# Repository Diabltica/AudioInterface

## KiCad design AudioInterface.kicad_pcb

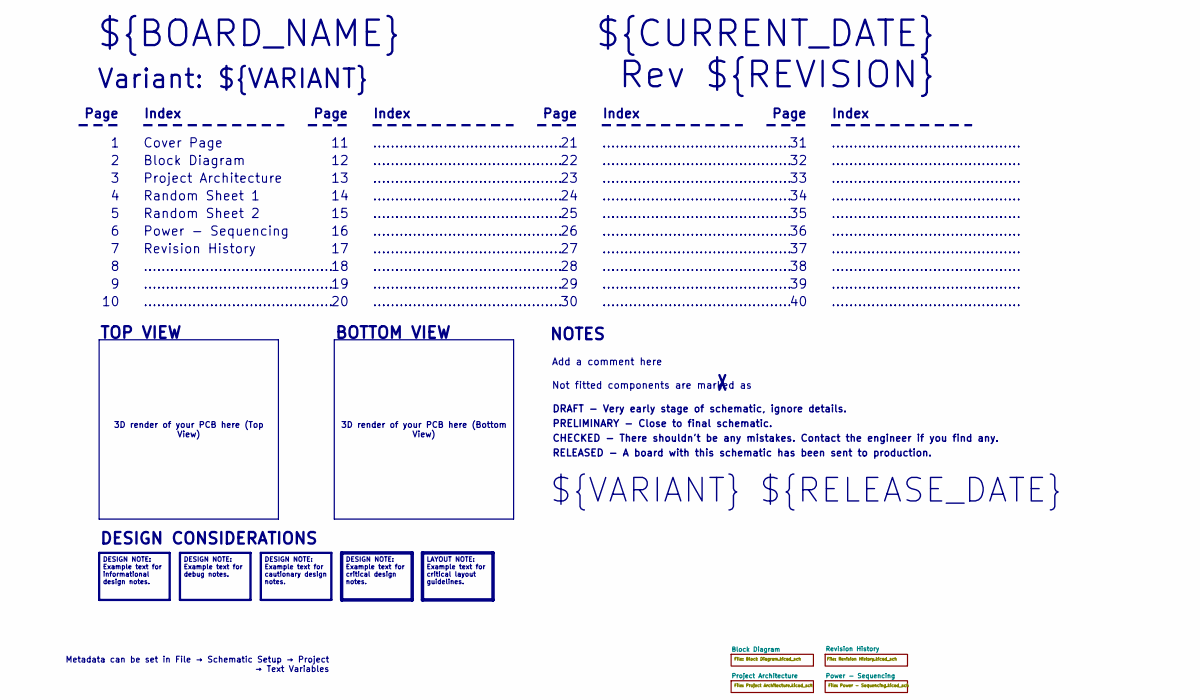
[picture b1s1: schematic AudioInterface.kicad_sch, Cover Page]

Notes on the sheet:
3D render of your PCB here (Bottom View)
3D render of your PCB here (Top View)
Metadata can be set in File → Schematic Setup → Project → Text Variables
DESIGN NOTE: Example text for informational design notes.
LAYOUT NOTE: Example text for critical layout guidelines.
DESIGN NOTE: Example text for cautionary design notes.
DESIGN NOTE: Example text for debug notes.
DESIGN NOTE: Example text for critical design notes.
BOTTOM VIEW
...........................................
RELEASED - A board with this schematic has been sent to production.
Page
TOP VIEW
Not fitted components are marked as
Index
PRELIMINARY - Close to final schematic.
${VARIANT} ${RELEASE_DATE}
Random Sheet 1
${CURRENT_DATE}
Variant: ${VARIANT}
Rev ${REVISION}
Random Sheet 2
${BOARD_NAME}
DRAFT - Very early stage of schematic, ignore details.
Power - Sequencing
Block Diagram
Add a comment here
Cover Page
NOTES
Project Architecture
CHECKED - There shouldn't be any mistakes. Contact the engineer if you find any.
DESIGN CONSIDERATIONS
Revision History

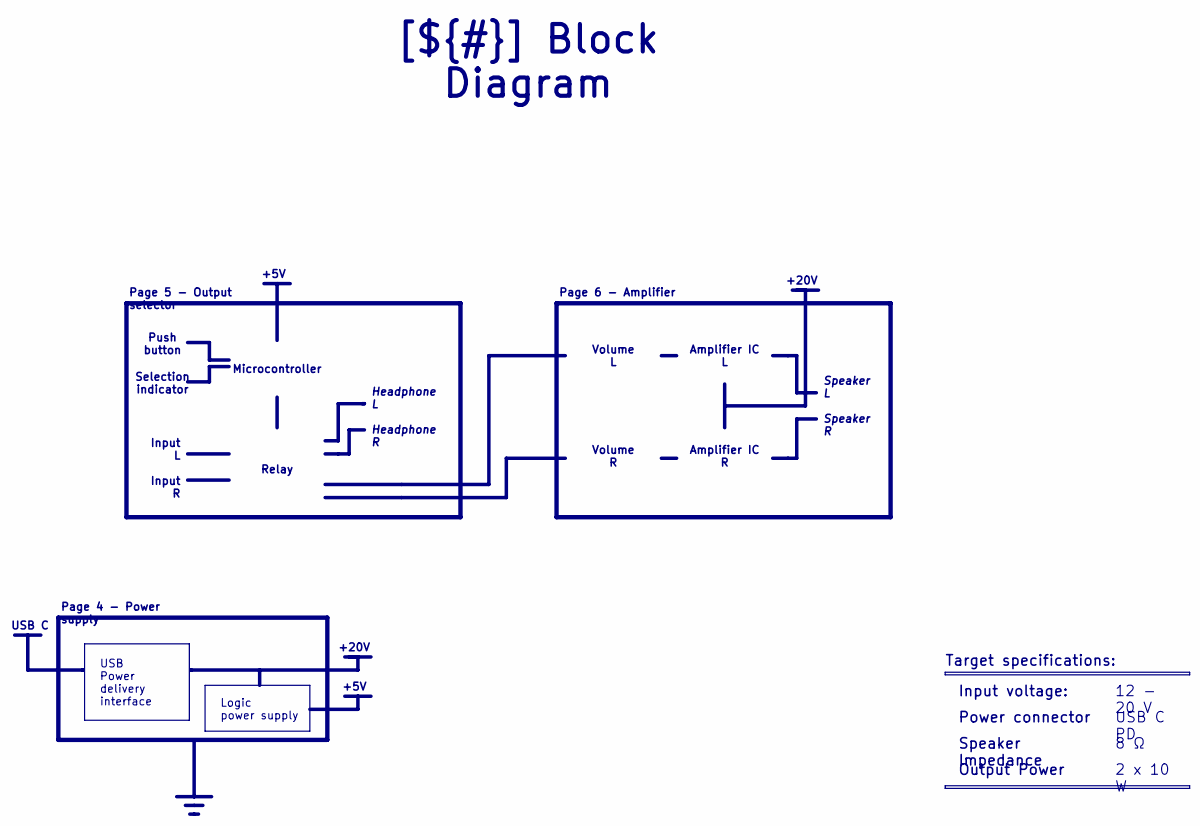
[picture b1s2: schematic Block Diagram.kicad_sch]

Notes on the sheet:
Page 5 - Output selector
Speaker Impedance
Power connector
Logic power supply
Input voltage:
2 x 10 W
USB C PD
Amplifier IC L
Volume L
Headphone L Headphone R
Microcontroller
[${#}] ${TITLE}
Page 4 - Power supply
Target specifications:
Selection indicator
8 Ω
Page 6 - Amplifier
12 - 20 V
Push button
Amplifier IC R
Relay
Input L Input R
Output Power
USB Power delivery interface
Volume R
Speaker L Speaker R
+20V
+5V
USB C

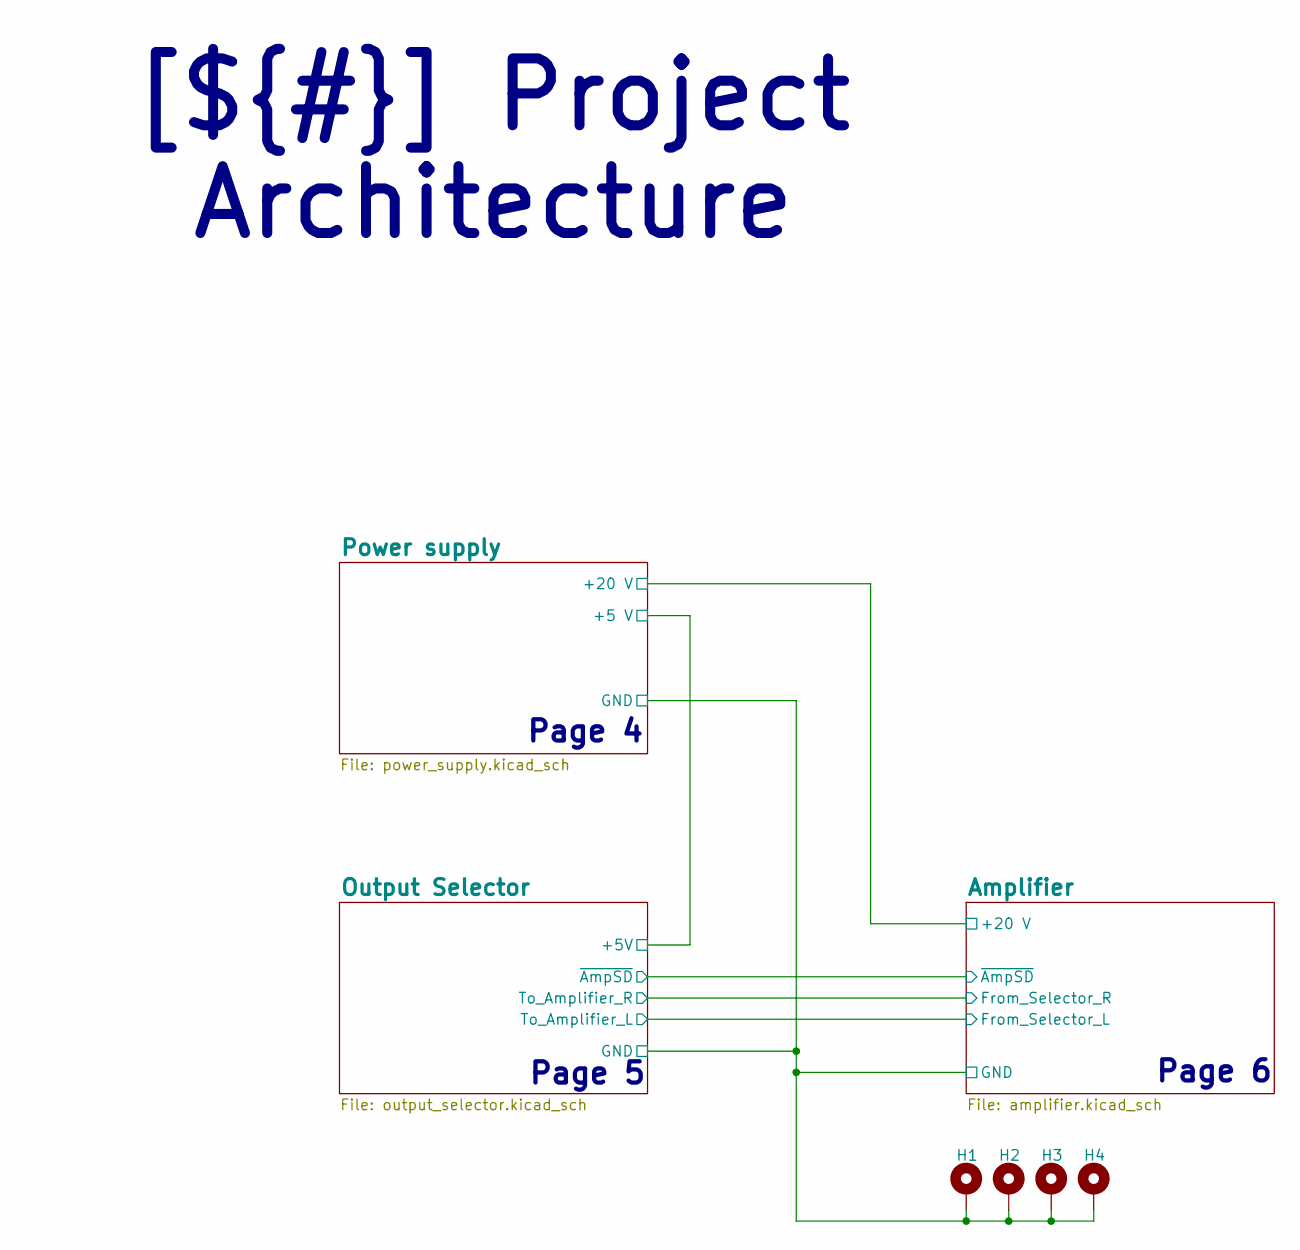
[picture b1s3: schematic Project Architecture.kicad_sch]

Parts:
H1, H2, H3, H4: MountingHole_Pad; MountingHole_3.2mm_M3_Pad_Via

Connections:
GND: H1.1, H2.1, H3.1, H4.1; also elsewhere on the board

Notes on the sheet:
[${#}] ${TITLE}
Page 6
Page 5
Page 4

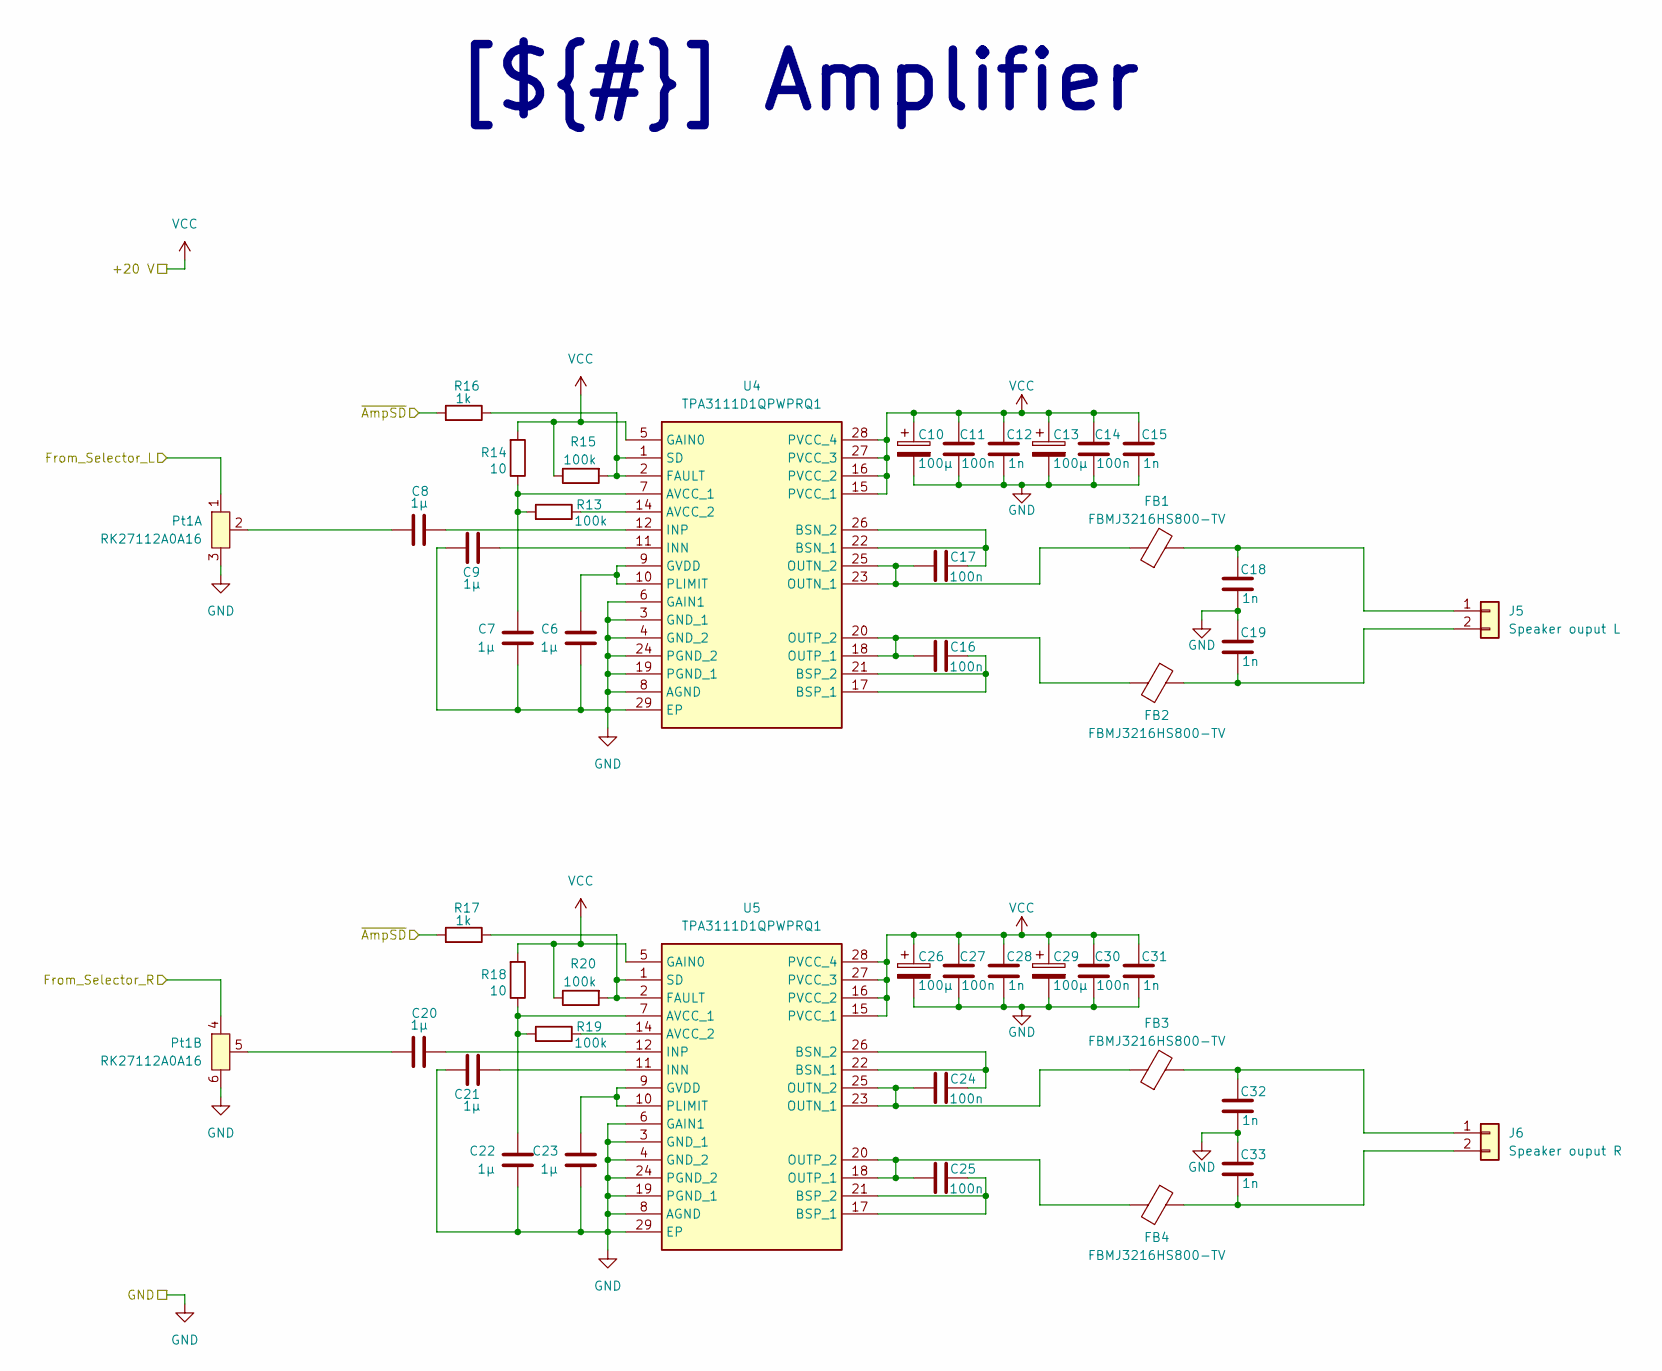
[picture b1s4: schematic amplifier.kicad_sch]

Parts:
C6, C7, C8, C9, C20, C21, C22, C23: 1µ; C_0402_1005Metric; LCSC Part C1518208
C10, C13, C26, C29: 100µ; CP_Elec_6.3x7.7; LCSC Part C178585
C11, C14, C16, C17, C24, C25, C27, C30: 100n; C_0402_1005Metric; LCSC Part C77020
C12, C15, C18, C19, C28, C31, C32, C33: 1n; C_0402_1005Metric; LCSC Part C77018
FB1, FB2, FB3, FB4: FBMJ3216HS800-TV; L_1206_3216Metric; LCSC C2661525
J5: Speaker ouput L; PinHeader_1x02_P2.54mm_Vertical
J6: Speaker ouput R; PinHeader_1x02_P2.54mm_Vertical
Pt1: RK27112A0A16; RES-ADJ-TH_RK27112A0A16; LCSC Part C470508
R13, R15, R19, R20: 100k; R_0402_1005Metric; LCSC Part C427253
R14, R18: 10; R_0402_1005Metric; LCSC Part C854481
R16, R17: 1k; R_0402_1005Metric; LCSC Part C427241
U4, U5: TPA3111D1QPWPRQ1; SOP65P640X120-29N; Mouser Part Number 595-TPA3111D1QPWPRQ1

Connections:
/Project Architecture/Amplifier/From_Selector_L: Pt1.1; also elsewhere on the board
/Project Architecture/Amplifier/From_Selector_R: Pt1.4; also elsewhere on the board
/Project Architecture/Amplifier/~AmpSD: R16.2, R17.2; also elsewhere on the board
GND: C6.1, C7.1, C9.2, C10.2, C11.1, C12.1, C13.2, C14.1, C15.1, C18.1, C19.2, C21.2, C22.1, C23.1, C26.2, C27.1, C28.1, C29.2, C30.1, C31.1, C32.1, C33.2, Pt1.3, Pt1.6, U4.3 (GND_1), U4.4 (GND_2), U4.6 (GAIN1), U4.8 (AGND), U4.19 (PGND_1), U4.24 (PGND_2), U4.29 (EP), U5.3 (GND_1), U5.4 (GND_2), U5.6 (GAIN1), U5.8 (AGND), U5.19 (PGND_1), U5.24 (PGND_2), U5.29 (EP); also elsewhere on the board
unnamed: C8.1, Pt1.2
unnamed: C20.1, Pt1.5
unnamed: C18.2, FB1.2, J5.1
unnamed: C19.1, FB2.1, J5.2
unnamed: C32.2, FB3.2, J6.1
unnamed: C33.1, FB4.1, J6.2
unnamed: C7.2, R13.2, R14.1, U4.7 (AVCC_1)
unnamed: R13.1, U4.14 (AVCC_2)
unnamed: C17.1, U4.22 (BSN_1), U4.26 (BSN_2)
unnamed: C16.1, U4.17 (BSP_1), U4.21 (BSP_2)
unnamed: R15.2, R16.1, U4.1 (SD), U4.2 (FAULT)
unnamed: C6.2, U4.9 (GVDD), U4.10 (PLIMIT)
unnamed: C9.1, U4.11 (INN)
unnamed: C8.2, U4.12 (INP)
unnamed: C17.2, FB1.1, U4.23 (OUTN_1), U4.25 (OUTN_2)
unnamed: C16.2, FB2.2, U4.18 (OUTP_1), U4.20 (OUTP_2)
unnamed: C22.2, R18.1, R19.2, U5.7 (AVCC_1)
unnamed: R19.1, U5.14 (AVCC_2)
unnamed: C24.1, U5.22 (BSN_1), U5.26 (BSN_2)
unnamed: C25.1, U5.17 (BSP_1), U5.21 (BSP_2)
unnamed: R17.1, R20.2, U5.1 (SD), U5.2 (FAULT)
unnamed: C23.2, U5.9 (GVDD), U5.10 (PLIMIT)
unnamed: C21.1, U5.11 (INN)
unnamed: C20.2, U5.12 (INP)
unnamed: C24.2, FB3.1, U5.23 (OUTN_1), U5.25 (OUTN_2)
unnamed: C25.2, FB4.2, U5.18 (OUTP_1), U5.20 (OUTP_2)
VCC: C10.1, C11.2, C12.2, C13.1, C14.2, C15.2, C26.1, C27.2, C28.2, C29.1, C30.2, C31.2, R14.2, R15.1, R18.2, R20.1, U4.5 (GAIN0), U4.15 (PVCC_1), U4.16 (PVCC_2), U4.27 (PVCC_3), U4.28 (PVCC_4), U5.5 (GAIN0), U5.15 (PVCC_1), U5.16 (PVCC_2), U5.27 (PVCC_3), U5.28 (PVCC_4); also elsewhere on the board

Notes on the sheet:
[${#}] ${TITLE}

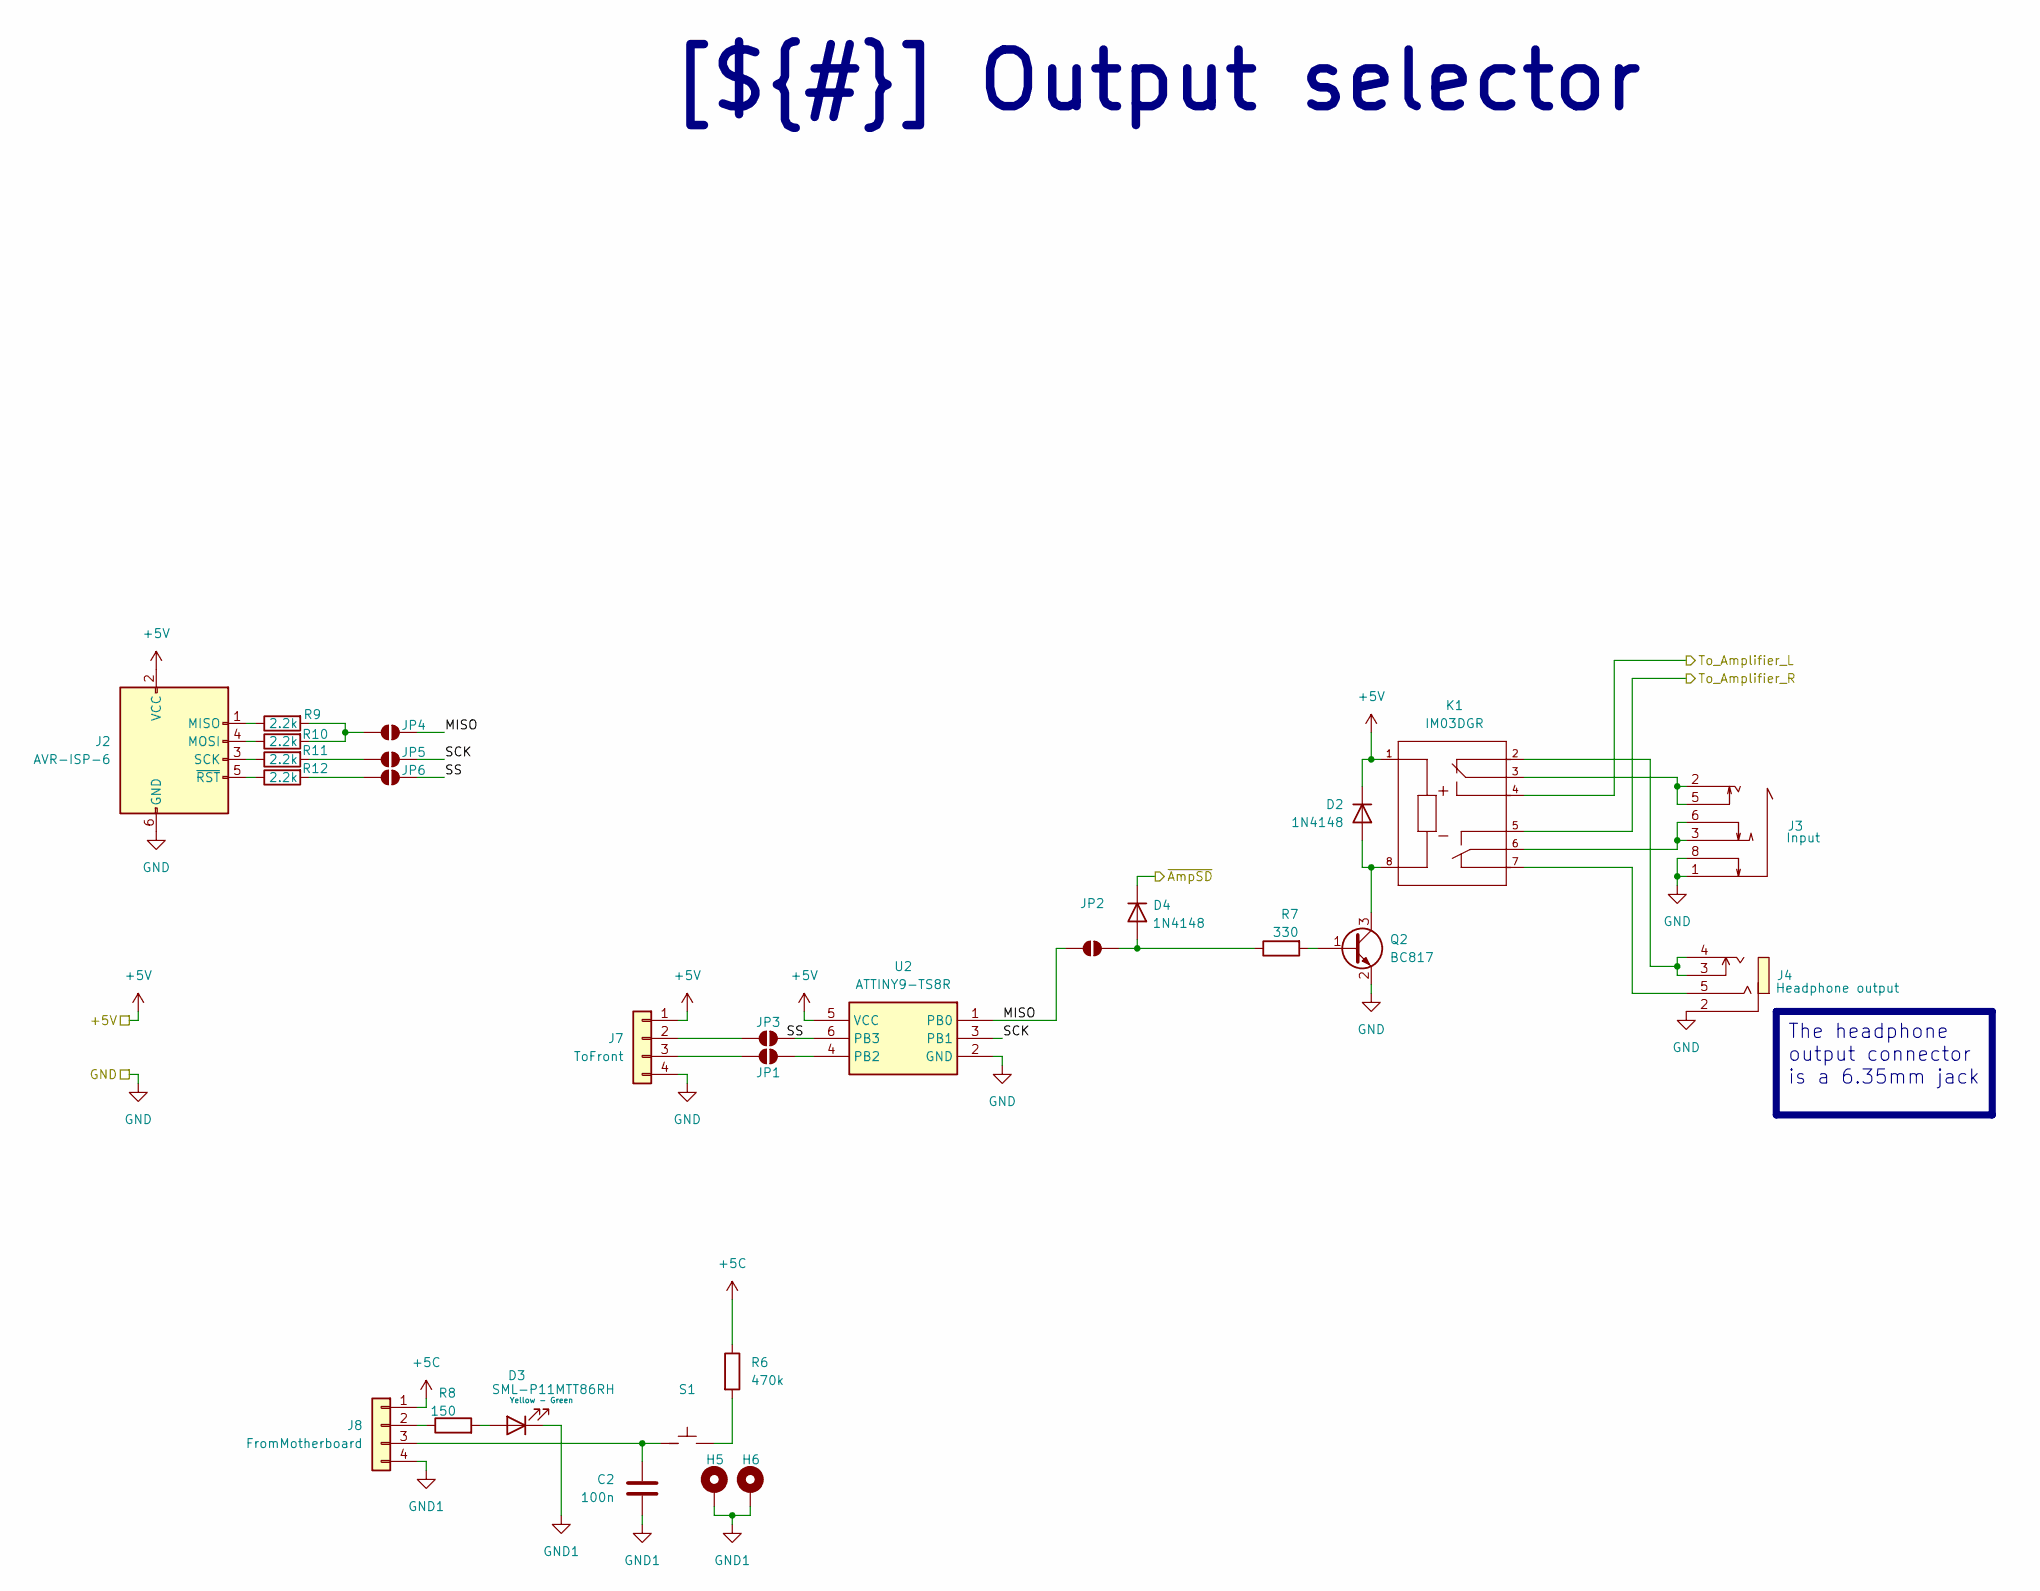
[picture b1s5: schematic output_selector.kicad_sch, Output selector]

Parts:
C2: 100n; C_0402_1005Metric; LCSC Part C77020
D2, D4: 1N4148; D_SOD-123; LCSC Part C5805632
D3: SML-P11MTT86RH; LED_0402_1005Metric; LCSC part C2898986
H5, H6: MountingHole_Pad; MountingHole_3.2mm_M3_Pad_Via
J2: AVR-ISP-6; PinSocket_2x03_P2.54mm_Vertical
J3: PJ-393-8P; AUDIO-TH_PJ-393-8A; LCSC Part C5155561
J4: PJ-603; AUDIO-TH_PJ-603; LCSC Part C309272
J7: ToFront; PinHeader_1x04_P2.54mm_Vertical
J8: FromMotherboard; PinHeader_1x04_P2.54mm_Vertical
JP1, JP2, JP3, JP4, JP5, JP6: SolderJumper_2_Open; SolderJumper-2_P1.3mm_Open_TrianglePad1.0x1.5mm
K1: IM03DGR; RELAY_IM03DGR; LCSC Part C5439567
Q2: BC817; SOT-23; LCSC Part C52801
R6: 470k; R_0402_1005Metric; LCSC Part C427256
R7: 330; R_0402_1005Metric; LCSC Part C427206
R8: 150; R_0402_1005Metric; LCSC Part C413067
R9, R10, R11, R12: 2.2k; R_0402_1005Metric; LCSC Part C427211
S1: PG151101S11; Kailh_socket_MX; PARTREV A; LCSC Part C41430893
U2: ATTINY9-TS8R; SOT95P270X145-6N; Mouser Part Number 556-ATTINY9-TS8R

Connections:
+5C: J8.1, R6.1
+5V: D2.1 (K), J2.2 (VCC), J7.1, K1.1, U2.5 (VCC); also elsewhere on the board
/Project Architecture/Amplifier/From_Selector_L: K1.4; also elsewhere on the board
/Project Architecture/Amplifier/From_Selector_R: K1.5; also elsewhere on the board
/Project Architecture/Amplifier/~AmpSD: D4.1 (K); also elsewhere on the board
/Project Architecture/Output Selector/MISO: JP2.1 (A), JP4.2 (B), U2.1 (PB0)
/Project Architecture/Output Selector/SCK: JP5.2 (B), U2.3 (PB1)
/Project Architecture/Output Selector/SS: JP3.1 (A), JP6.2 (B), U2.6 (PB3)
GND: J2.6 (GND), J3.1, J3.8, J4.2, J7.4, Q2.2 (E), U2.2 (GND); also elsewhere on the board
GND1: C2.1, D3.1 (K), H5.1, H6.1, J8.4
unnamed: D2.2 (A), K1.8, Q2.3 (C)
unnamed: D3.2 (A), R8.2
unnamed: D4.2 (A), JP2.2 (B), R7.1
unnamed: J2.1 (MISO), R9.1
unnamed: J2.4 (MOSI), R10.1
unnamed: J2.3 (SCK), R11.1
unnamed: J2.5 (~RST), R12.1
unnamed: J3.2, J3.5, K1.3
unnamed: J3.3, J3.6, K1.6
unnamed: J4.3, J4.4, K1.2
unnamed: J4.5, K1.7
unnamed: J7.2, JP3.2 (B)
unnamed: J7.3, JP1.1 (A)
unnamed: J8.2, R8.1
unnamed: C2.2, J8.3, S1.2
unnamed: JP1.2 (B), U2.4 (PB2)
unnamed: JP4.1 (A), R9.2, R10.2
unnamed: JP5.1 (A), R11.2
unnamed: JP6.1 (A), R12.2
unnamed: Q2.1 (B), R7.2
unnamed: R6.2, S1.1

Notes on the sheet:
[${#}] ${TITLE}
The headphone output connector is a 6.35mm jack

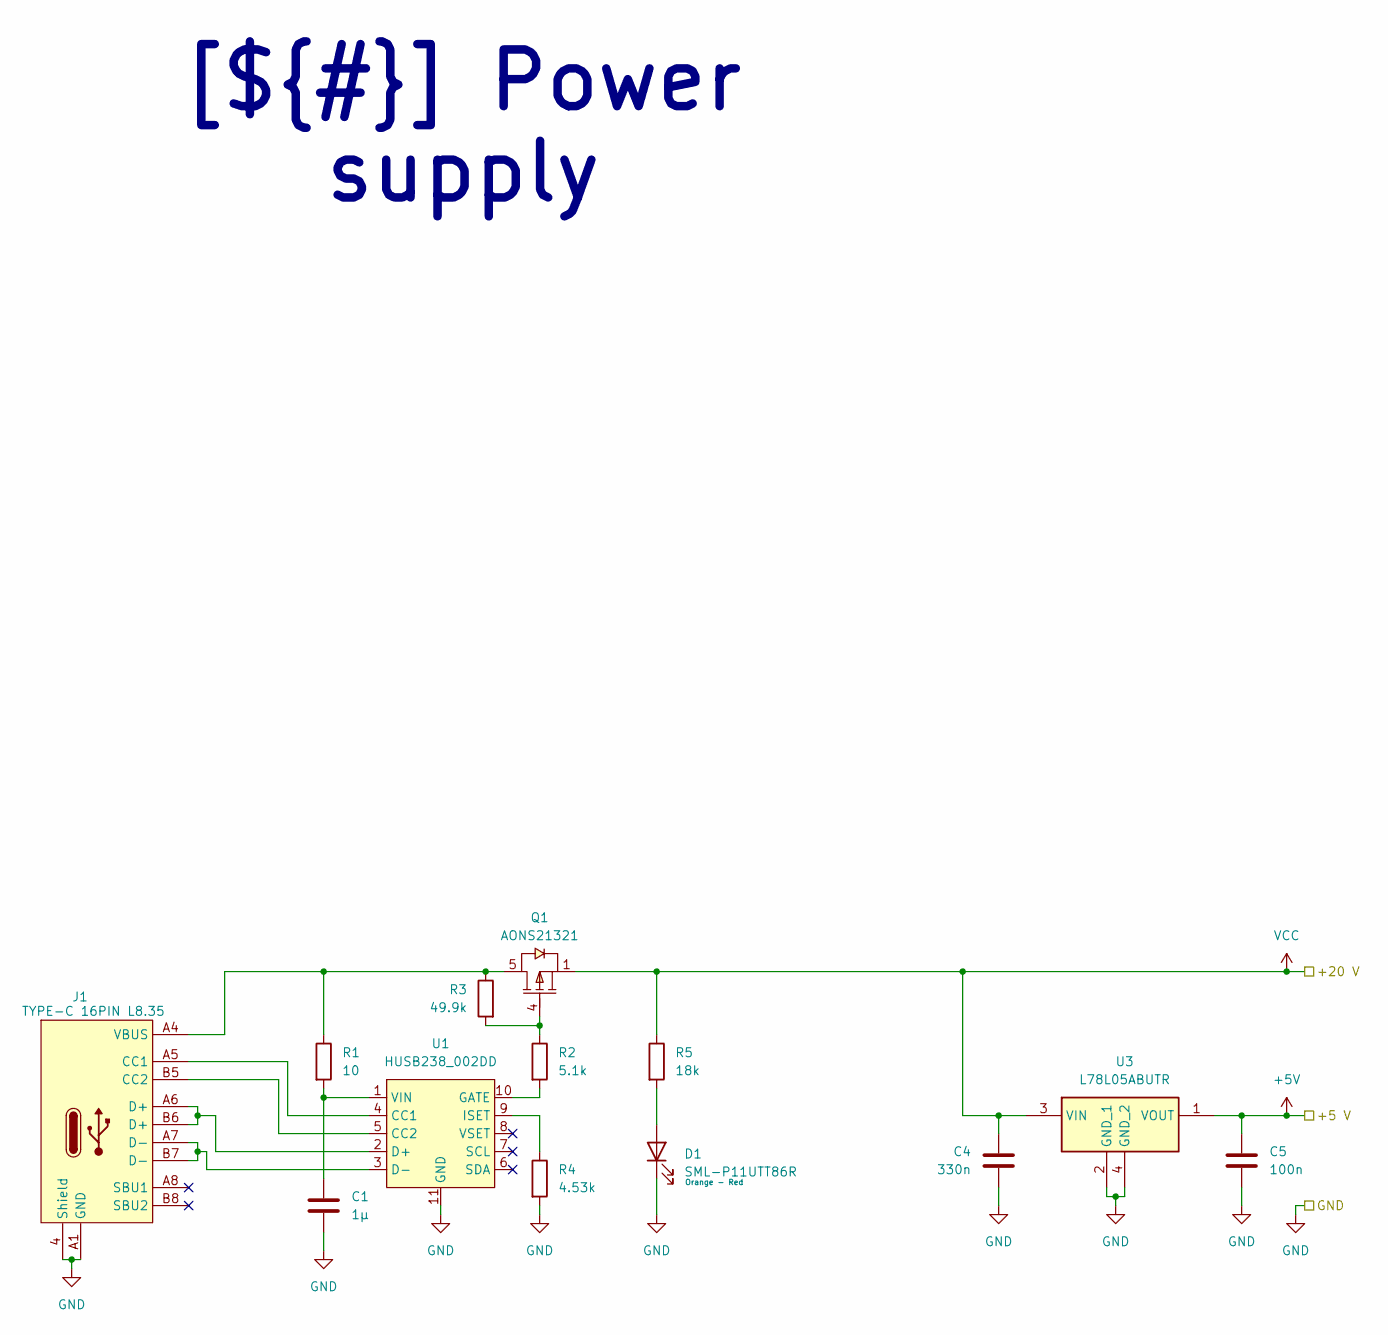
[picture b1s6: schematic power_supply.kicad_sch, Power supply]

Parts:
C1: 1µ; C_0402_1005Metric; LCSC Part C1518208
C4: 330n; C_0402_1005Metric; LCSC Part C16193239
C5: 100n; C_0402_1005Metric; LCSC Part C77020
D1: SML-P11UTT86R; LED_0402_1005Metric; LCSC part C510300
J1: TYPE-C 16PIN L8.35; TYPE-C-SMD_20009-UCAF001-X; LCSC Part C5379909
Q1: AONS21321; DFN-8_L6.0-W5.0-P1.27-LS6.2-BL; LCSC Part C5143571
R1: 10; R_0402_1005Metric; LCSC Part C854481
R2: 5.1k; R_0603_1608Metric; LCSC Part C413696
R3: 49.9k; R_0402_1005Metric; LCSC Part C409918
R4: 4.53k; R_0402_1005Metric; LCSC Part C416543
R5: 18k; R_0402_1005Metric; LCSC Part C413008
U1: HUSB238_002DD; DFN-10_L3.0-W3.0-P0.50-BL-EP2.5; LCSC Part C7471904
U3: L78L05ABUTR; Mouser Part Number 511-L78L05ABU

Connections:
+5V: C5.2, U3.1 (VOUT); also elsewhere on the board
GND: C1.1, C4.1, C5.1, D1.1 (K), J1.4 (Shield), J1.A1 (GND), R4.2, U1.11 (GND), U3.2 (GND_1), U3.4 (GND_2); also elsewhere on the board
unnamed: D1.2 (A), R5.2
unnamed: J1.A5 (CC1), U1.4 (CC1)
unnamed: J1.B5 (CC2), U1.5 (CC2)
unnamed: J1.A4 (VBUS), Q1.5 (D), R1.1, R3.1
unnamed: Q1.4 (G), R2.1, R3.2
unnamed: J1.A6 (D+), J1.B6 (D+), U1.2 (D+)
unnamed: J1.A7 (D-), J1.B7 (D-), U1.3 (D-)
unnamed: R2.2, U1.10 (GATE)
unnamed: R4.1, U1.9 (ISET)
unnamed: C1.2, R1.2, U1.1 (VIN)
VCC: C4.2, Q1.1 (S), R5.1, U3.3 (VIN); also elsewhere on the board

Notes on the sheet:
[${#}] ${TITLE}

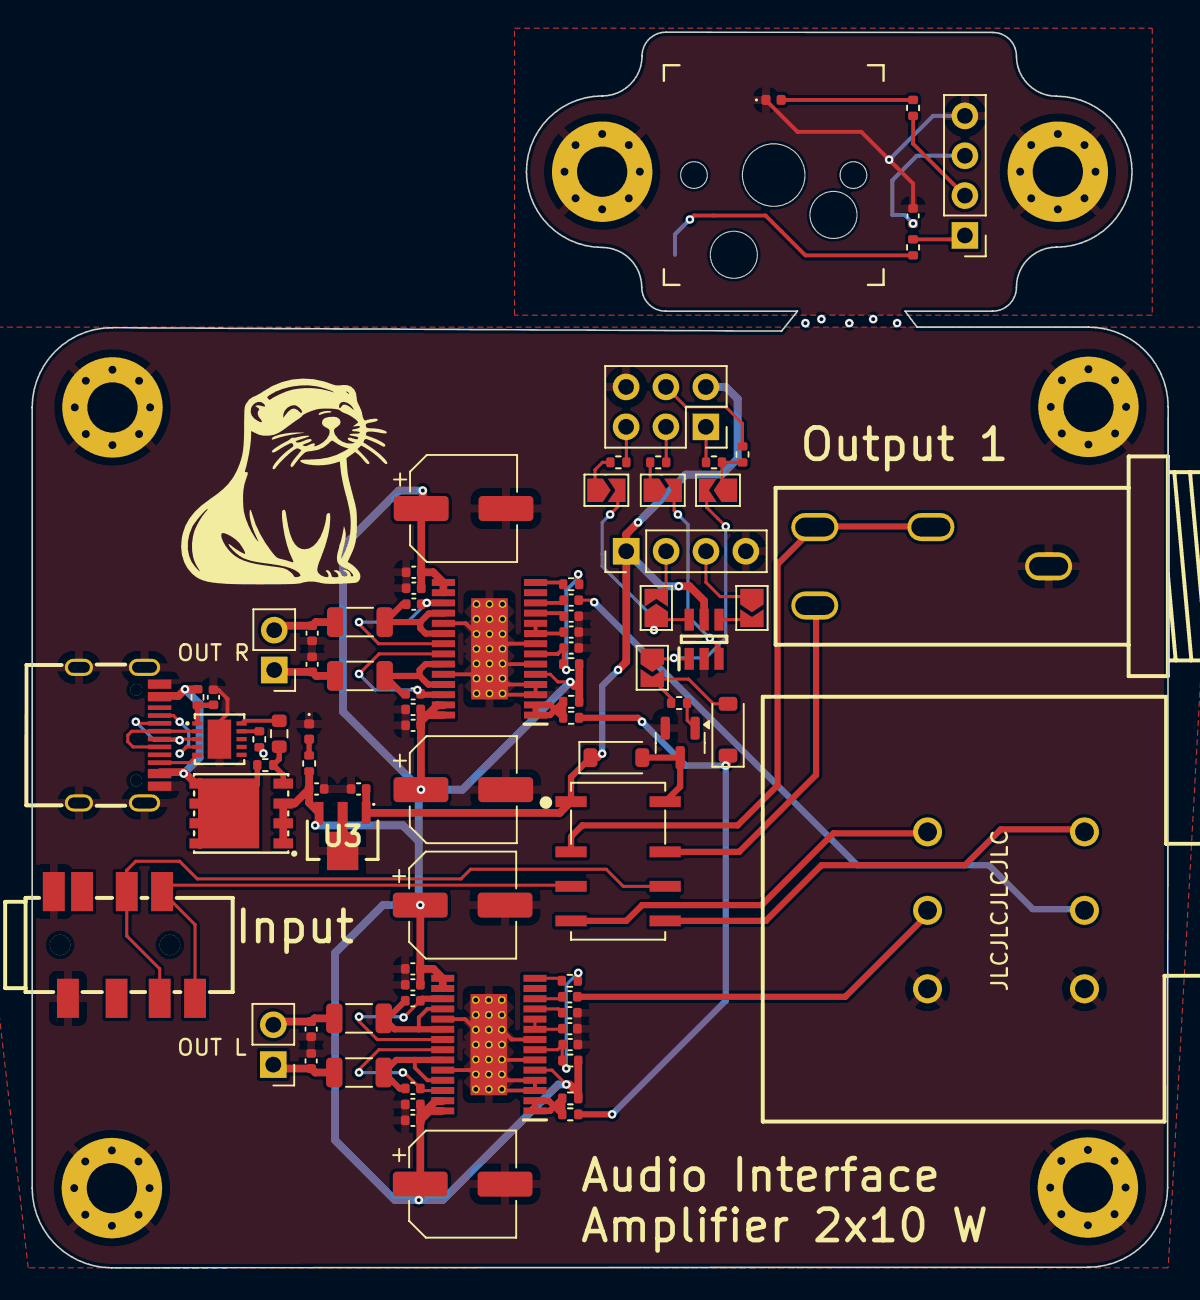
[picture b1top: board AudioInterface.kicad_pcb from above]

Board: 2 copper layers, 72.4 x 78.7 mm, 90 parts (0 on the bottom side), 68 nets.

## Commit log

2024-12-19 add file
2024-12-19 add missing folder
2024-12-21 power supply first draft
2024-12-21 Add output selector
2024-12-21 add 5V regulator
2024-12-21 CI draft
2024-12-21 add kibot config
2024-12-21 move config file
2024-12-21 change file path
2024-12-21 remove useless folder
2024-12-22 rename workflow config and remove drc check
2024-12-22 update config to export schematic documentation
2024-12-22 change job name
2024-12-22 add needs and fix indentation
2024-12-22 fix typo
2024-12-22 place component on pcb to generate bom
2024-12-22 fix path
2024-12-22 remove drc
2024-12-22 add download artifact step
2024-12-22 add path to download artifact
2024-12-22 remove useless ls
2024-12-22 deploy page
2024-12-22 fix need
2024-12-22 install sudo
2024-12-22 test
2024-12-22 add ls
2024-12-22 fix ls path
2024-12-22 draft amplifier circuit
2024-12-23 Finish amplifier, add shutdown control
2024-12-23 change C10, C13, C24, C29 to polarized capacitor
2024-12-23 complete wiring
2024-12-23 source component and fix some lib
2024-12-24 add connector to separate the selector switch and led indicator
2024-12-24 update footprint
2024-12-24 finish pcb and generate production file
